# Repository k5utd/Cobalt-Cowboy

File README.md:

# Cobalt-Cowboy

A RISC-V-based digital mode radio running OpenRTX Radio Firmware

The goal of this project is to make available a hackable radio development platform for evaluating radio transceivers and experimenting with amateur multi-mode radio technology.

The intended users of this project include licenced Amateur Radio operators and students.

> [!NOTE]
> This repository includes the PCB, Schematic, and associated [KiCAD](https://www.kicad.org/) project files, as well as a parts list and any information necessary to build your own Cobalt Cowboy.

## Background

### OpenRTX Real-Time Operating Systems

This project intends to leverage the growing RF vendor support of Zephyr Project [ZephyrRTOS](https://zephyrproject.org/learn-about/).

The [OpenRTX firmware](https://openrtx.org) is an RTOS-agnostic application built from the ground-up with digital mode radios (DMR) in mind, some of which support the M17 protocol with hardware modification after firmware flashing.

The OpenRTX firmware typically uses the [Miosix](https://miosix.org/) kernel, primarily supporting STM32 targets on the ARM Cortex-M4F architecture, and is being ported to ZephyrRTOS to take advantage of support for more architectures.

### M17 Digital Mode and Codec2

For the purposes of this project, having multiple vocoder options to choose from for digital mode operation is desirable for reducing vendor lockin and avoiding product obsolescence.

The [M17 Project](https://m17project.org/) M17 RF protocol is an open protocol specification that leverages [Codec2](https://en.wikipedia.org/wiki/Codec_2) instead of DVSI [AMBE](https://en.wikipedia.org/wiki/Multi-Band_Excitation). 

Codec2 allows for open implementations as a software-defined vocoding alternative to DVSI vocoding hardware, complimenting the open communication stack of M17.

### Limitations and Alternatives 

The LILYGO [T-TWR Plus](https://www.lilygo.cc/products/t-twr-rev2-1) is a development board for evaluating the `NiceRF SA868` Walkie Talkie and `Quectel L76K` GNSS modules. The T-TWR Plus is as of September 2023 what motivated the OpenRTX team to begin porting OpenRTX to ZephyrRTOS. As of July 2024, rev2.1 now shows promise for experimenting with software-defined digital mode radio on VHF or UHF with improved RF module interfacing.

LILYGO has maintains a [repository](https://github.com/Xinyuan-LilyGO/T-TWR) of example testing firmware and schematics, However, the T-TWR Plus is not necessarily open source hardware, being schematic-available with no manufacturing files. NiceRF does not maintain public factory firmware of the SA868 either, so OpenRTX [sa8x8-fw](https://github.com/OpenRTX/sa8x8-fw) is necessary for use with OpenRTX.

## Getting Started

> [!IMPORTANT]
> This repository is primarily the hardware, the firmware and instructions are to be made available upstream OpenRTX.

### Board Fabrication

The board stackup is intended for OSHPark fabrication services.

The main board features an Espressif `ESP32-C3` and integrates the Texas Instruments `CC1200` Sub-Ghz transceiver. Most components are surface mount, and can get as small as `0602`.

### Firmware 
1. Set up the [Zephyr](https://docs.zephyrproject.org/latest/develop/getting_started/index.html) development environment
2. Set up the [Zephyr-based target toolchain](https://openrtx.org/#/compiling?id=compiling-a-zephyr-based-target) for OpenRTX
3. TODO: Build and compile an OpenRTX image for the `cobalt-cowboy` target

## Contact

To reach out, please join the Discord server.

CO: [Eric Mutton](https://github.com/ericmutton), username `cyndre`.

## License

This project is released under the GNU GPL v3.

See [LICENSE](LICENSE)

## Credits

Our thanks go to the following organizations for their efforts and advice:
* [M17 Project](https://m17project.org/) for their digital radio protocol for data and voice
* [OpenRTX](https://openrtx.org) for their radio firmware for digital mode radios and ham devices

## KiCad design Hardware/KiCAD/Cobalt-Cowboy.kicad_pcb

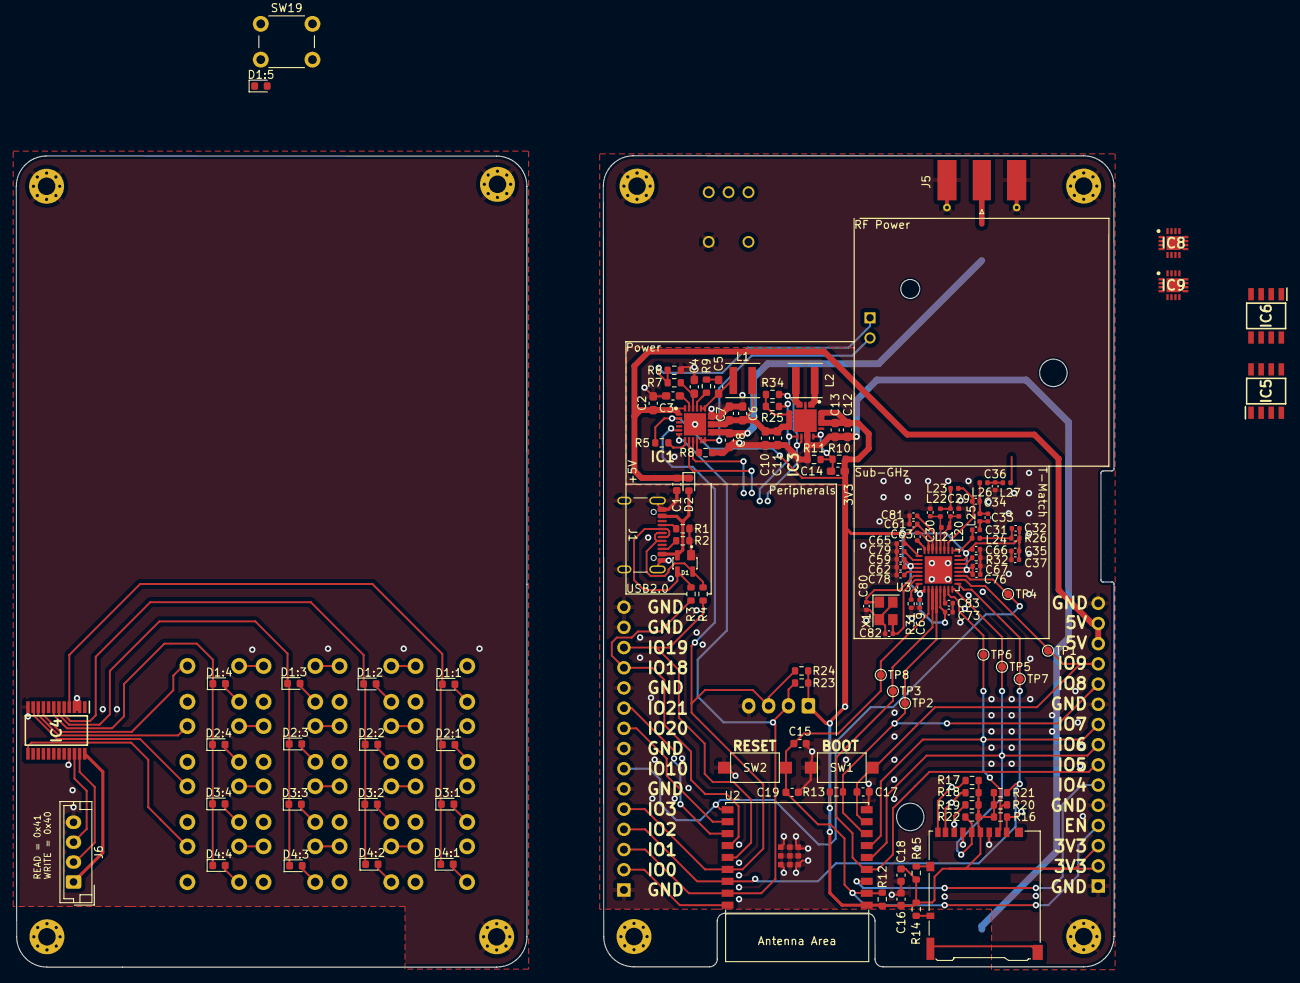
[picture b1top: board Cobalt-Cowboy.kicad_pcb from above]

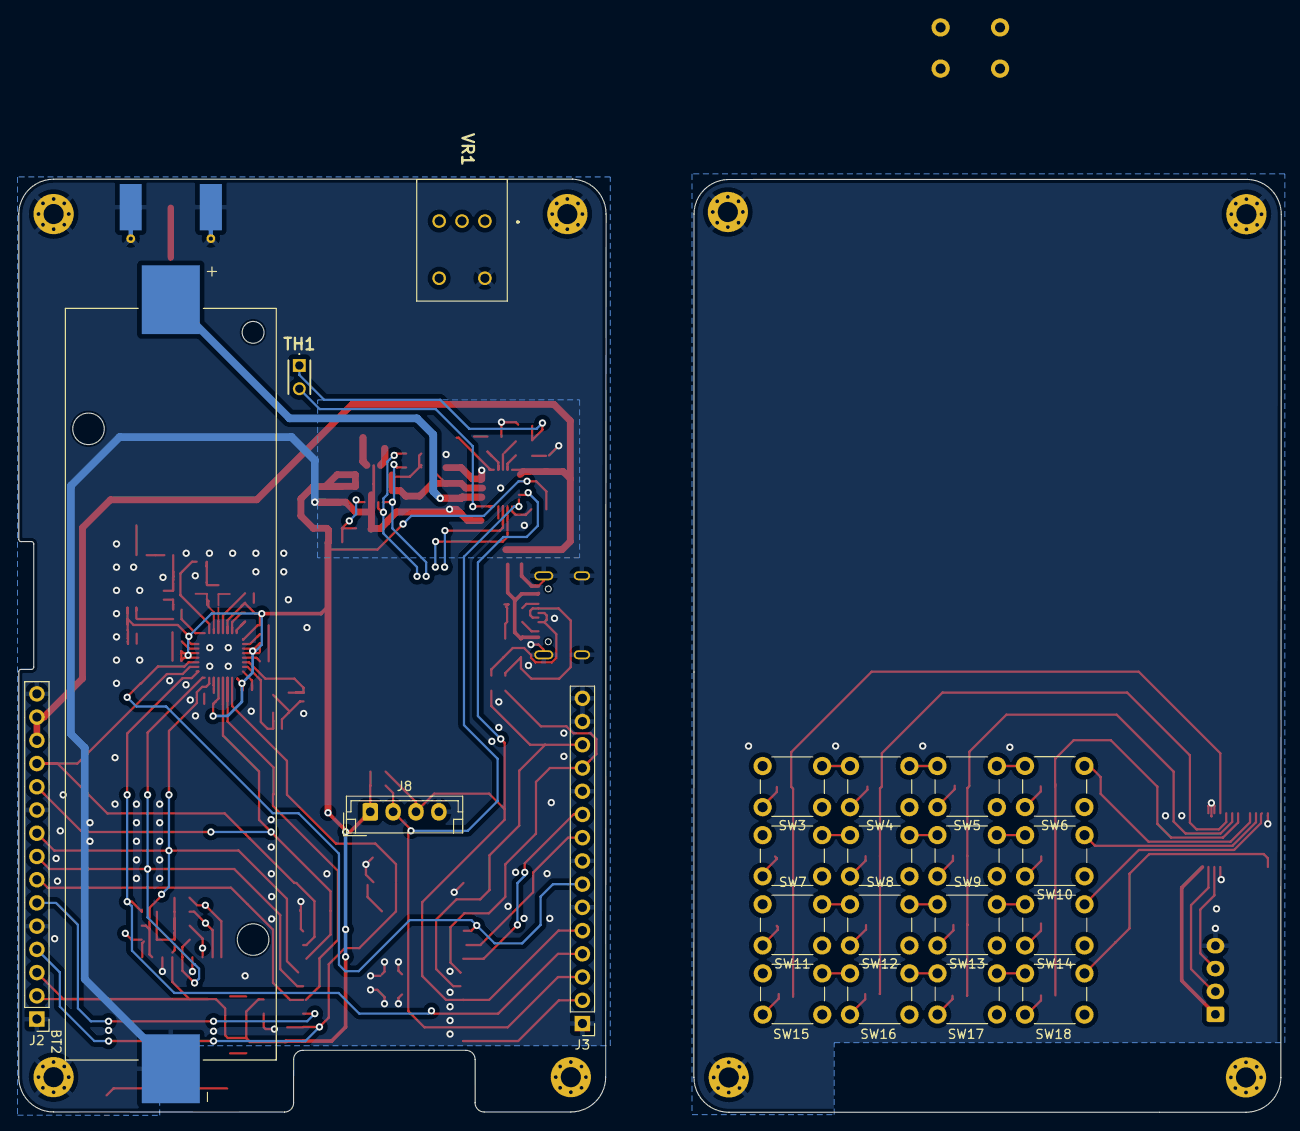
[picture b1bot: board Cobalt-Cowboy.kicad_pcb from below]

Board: 2 copper layers, 138.1 x 102.0 mm, 156 parts (22 on the bottom side), 98 nets.

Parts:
BT2: 1122; BAT_1122
C1, C16: 10u; C_0603_1608Metric
C2, C3: 1u; C_0603_1608Metric_Pad1.08x0.95mm_HandSolder
C4: 1uF; C_0603_1608Metric_Pad1.08x0.95mm_HandSolder
C5: 47n; C_0603_1608Metric_Pad1.08x0.95mm_HandSolder
C6, C7, C8, C10, C11: 10u; C_0603_1608Metric_Pad1.08x0.95mm_HandSolder
C12, C13: 22u; C_0603_1608Metric_Pad1.08x0.95mm_HandSolder
C14: 56p; C_0603_1608Metric_Pad1.08x0.95mm_HandSolder
C15: 1u; C_0603_1608Metric
C17, C18, C19: 0.1u; C_0603_1608Metric
C29, C30, C34: 5.1p; C_0402_1005Metric
C31: 39p; C_0402_1005Metric
C32: 56p; C_0402_1005Metric
C33: 2.2p; C_0402_1005Metric
C35, C81: 10n; C_0402_1005Metric
C36: 6.2p; C_0402_1005Metric
C37: 100p; C_0402_1005Metric
C59, C61, C62, C65, C66, C67, C69, C73, C76, C78, C79: 47n; C_0402_1005Metric
C63: 1.5n; C_0402_1005Metric
C80, C82: 15p; C_0402_1005Metric
C83: 220n; C_0402_1005Metric
D1: SP0503BAHTG; SOT143
D1:1, D1:2, D1:3, D1:4, D1:5, D2:1, D2:2, D2:3, D2:4, D3:1, D3:2, D3:3, D3:4, D4:1, D4:2, D4:3, D4:4: D; D_0603_1608Metric
D2: 1N5819; D_0603_1608Metric
IC1: BQ24193RGER; QFN50P400X400X100-25N-D_BQ24193RGER
IC3: ISL91127IRNZ-T7A; QFN50P400X400X100-21N_ISL91127IRNZ-T7A
IC4: PCF8575PWR; SOP65P640X120-24N_PCF8575PWR
IC5, IC6: SA630D_01,118; SOIC127P600X175-8N_SA630D_01,118
IC8, IC9: GRF5504; QFN50P300X300X90-17N_GRF5504
J1: USB_C_Receptacle; USB_C_Receptacle_GCT_USB4105-xx-A_16P_TopMnt_Horizontal
J2, J3: 1x15; PinHeader_1x15_P2.54mm_Vertical
J4: SD_Card; microSD_HC_Hirose_DM3AT-SF-PEJM5
J5: Conn_Coaxial_UHF; SMA_Molex_73251-1153_EdgeMount_Horizontal
J6, J8: Peripherals; JST_EH_B4B-EH-A_1x04_P2.50mm_Vertical
L1: 2.2u; L_Coilcraft_XxL4020
L2: 1u; L_Coilcraft_XxL4020
L20, L22: 27n; L_0402_1005Metric
L21, L24: 56n; L_0402_1005Metric
L23, L25: 15n; L_0402_1005Metric
L26: 43n; L_0402_1005Metric
L27: 22n; L_0402_1005Metric
R1: 5.1K; R_0603_1608Metric
R2: 5.1k; R_0603_1608Metric
R3, R4: 0k; R_0603_1608Metric
R5, R12, R13, R14, R15, R16, R17, R18, R19, R20, R21, R22, R23, R24, R25, R34: 10k; R_0603_1608Metric
R6: 6.86k; R_0603_1608Metric
R7: 2.27k; R_0603_1608Metric
R8: 265R; R_0603_1608Metric
R9: 0R; R_0603_1608Metric
R10: 1M; R_0603_1608Metric
R11: 2.2M; R_0603_1608Metric
R26: 18; R_0402_1005Metric
R31: 0R; R_0402_1005Metric
R32: 56k; R_0402_1005Metric
REF1, REF2, REF3, REF4, REF5, REF6, REF7, REF8: Conn_01x01; MountingHole_2.2mm_M2_Pad_Via
SW1, SW2: SW_Push; SW_SPST_CK_RS282G05A3
SW3: MENU; SW_PUSH_6mm_H7.3mm
SW4: UP; SW_PUSH_6mm_H7.3mm
SW5: DOWN; SW_PUSH_6mm_H7.3mm
SW6: EXIT; SW_PUSH_6mm_H7.3mm
SW7: 1; SW_PUSH_6mm_H7.3mm
SW8: 2; SW_PUSH_6mm_H7.3mm
SW9: 3; SW_PUSH_6mm_H7.3mm
SW10: *; SW_PUSH_6mm_H7.3mm
SW11: 4; SW_PUSH_6mm_H7.3mm
SW12: 5; SW_PUSH_6mm_H7.3mm
SW13: 6; SW_PUSH_6mm_H7.3mm
SW14: 0; SW_PUSH_6mm_H7.3mm
SW15: 7; SW_PUSH_6mm_H7.3mm
SW16: 8; SW_PUSH_6mm_H7.3mm
SW17: 9; SW_PUSH_6mm_H7.3mm
SW18: #; SW_PUSH_6mm_H7.3mm
SW19: PTT; SW_PUSH_6mm_H7.3mm
TH1: 103AT-2; 103AT2
TP1, TP2, TP3, TP4, TP5, TP6, TP7, TP8: TestPoint; TestPoint_Pad_D1.0mm
U2: ESP32-C3-WROOM-02
U3: CC1200RHBR; QFN-32-1EP_5x5mm_P0.5mm_EP3.45x3.45mm
VR1: RK09711110EL
X1: 40 MHz; Crystal_SMD_3225-4Pin_3.2x2.5mm

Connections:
3.3V: C12.1, C13.1, C14.1, C16.1, C18.2, C32.1, C35.1, C37.1, C59.1, C61.1, C62.1, C65.1, C66.1, C67.1, C69.1, C73.1, C76.1, IC1.2 (PSEL), IC3.17 (VOUT_1), IC3.18 (VOUT_2), IC3.19 (VOUT_3), IC3.20 (VOUT_4), IC4.24 (VCC), J2.2, J2.3, J4.4 (VDD), J6.1, J8.1, R5.1, R10.1, R12.2, R13.2, R14.2, R15.2, R16.2, R17.2, R18.2, R19.2, R20.2, R21.2, R22.2, R23.1, R24.1, R26.1, U2.1 (3V3), U3.1 (VDD_GUARD), U3.5 (DVDD), U3.12 (DVDD), U3.13 (AVDD_IF), U3.15 (AVDD_RF), U3.22 (AVDD_SYNTH1), U3.25 (AVDD_PFD_CHP), U3.27 (AVDD_SYNTH2), U3.28 (AVDD_XOSC)
+BATT: BT2.P, C8.1, IC1.13 (BAT_1), IC1.14 (BAT_2)
/Antenna_System/Amplifier_Assembly/5v_Amplifier_VCC: IC8.12 (BIAS), IC9.12 (BIAS)
/Antenna_System/LNA_N: C30.1, L21.2, L22.1, U3.20 (LNA_N)
/Antenna_System/LNA_P: C29.1, L20.1, L21.1, U3.19 (LNA_P)
/Antenna_System/PA: C31.2, L24.1, U3.17 (PA)
/Antenna_System/RF_Signal: IC5.3 (INPUT), L27.2
/Antenna_System/TRX_SW: C34.2, L23.1, U3.18 (TRX_SW)
/Communications_System/CC_X1: C80.2, U3.30 (XOSC_Q1), X1.1
/Communications_System/CC_X2: C82.1, U3.31 (XOSC_Q2), X1.3
/Computing_System/GPIO0: J3.2, U2.18 (GPIO0/ADC1_CH0/XTAL_32K_P)
/Computing_System/GPIO4: J2.6, U2.3 (GPIO4/ADC1_CH4)
/Computing_System/GPIO5: J2.7, TP3.1, U2.4 (GPIO5/ADC2_CH0), U3.3 (GPIO3)
/Computing_System/GPIO8: J2.11, R13.1, TP2.1, U2.7 (GPIO8), U3.4 (GPIO2)
/Computing_System/GPIO9: C17.2, J2.12, SW1.2, TP1.1, U2.8 (GPIO9), U3.10 (GPIO0)
/Computing_System/GPIO10: J3.7, TP4.1, U2.10 (GPIO10), U3.11 (~CS)
/Computing_System/I2C0_SCL: IC1.5 (SCL), IC4.22 (SCL), J3.5, J6.3, J8.3, R24.2, U2.15 (GPIO3/ADC1_CH3)
/Computing_System/I2C0_SDA: IC1.6 (SDA), IC4.23 (SDA), J3.3, J6.2, J8.2, R23.2, U2.17 (GPIO1/ADC1_CH1/XTAL_32K_N)
/Computing_System/Keypad/COL1: D1:1.1 (K), D2:1.1 (K), D3:1.1 (K), D4:1.1 (K), IC4.4 (P00)
/Computing_System/Keypad/COL2: D1:2.1 (K), D2:2.1 (K), D3:2.1 (K), D4:2.1 (K), IC4.5 (P01)
/Computing_System/Keypad/COL3: D1:3.1 (K), D2:3.1 (K), D3:3.1 (K), D4:3.1 (K), IC4.6 (P02)
/Computing_System/Keypad/COL4: D1:4.1 (K), D2:4.1 (K), D3:4.1 (K), D4:4.1 (K), IC4.7 (P03)
/Computing_System/Keypad/COL5: D1:5.1 (K), IC4.8 (P04)
/Computing_System/Keypad/ROW1: IC4.9 (P05), SW3.2, SW4.2, SW5.2, SW6.2, SW19.2
/Computing_System/Keypad/ROW2: IC4.10 (P06), SW7.2, SW8.2, SW9.2, SW10.2
/Computing_System/Keypad/ROW3: IC4.11 (P07), SW11.2, SW12.2, SW13.2, SW14.2
/Computing_System/Keypad/ROW4: IC4.13 (P10), SW15.2, SW16.2, SW17.2, SW18.2
/Computing_System/RST: C15.2, C19.2, J2.4, R12.1, SW2.2, TP8.1, U2.2 (EN/CHIP_PU), U3.2 (~RESET)
/Computing_System/SD_DAT0: J4.7 (DAT0), R19.1
/Computing_System/SD_DAT1: J4.8 (DAT1), R18.1
/Computing_System/SD_DAT2: J4.9 (DAT2), R17.1
/Computing_System/SD_DAT3: J4.1 (CD/DAT3), R16.1
/Computing_System/SPIM2_MISO: J3.4, R21.1, TP7.1, U2.16 (GPIO2/ADC1_CH2), U3.9 (SO(GPIO1))
/Computing_System/SPIM2_MOSI: J2.9, J4.2 (CMD), R20.1, TP6.1, U2.6 (GPIO7), U3.7 (SI)
/Computing_System/SPIM2_SCLK: J2.8, J4.5 (CLK), R22.1, TP5.1, U2.5 (GPIO6), U3.8 (SCLK)
/Computing_System/UART0_RX: J3.9, U2.11 (GPIO20/U0RXD)
/Computing_System/UART0_TX: J3.10, U2.12 (GPIO21/U0TXD)
/Computing_System/~SD_CD: J4.10 (CARD_DETECT), R14.1
/Computing_System/~SD_WP: J4.11 (WRITE_PROTECT), R15.1
/Power_System/BMS_INT: IC1.7 (INT), R5.2
/Power_System/V_{SYS}: C6.2, C7.2, C10.2, C11.2, IC1.15 (SYS_1), IC1.16 (SYS_2), IC3.6 (PVIN_1), IC3.7 (PVIN_2), IC3.8 (PVIN_3), IC3.9 (PVIN_4), IC3.10 (VIN), L1.2, R25.1, R34.2
/USB_DN: J3.12, R3.2, U2.13 (GPIO18/USB_D-)
/USB_DP: J3.13, R4.1, U2.14 (GPIO19/USB_D+)
GND: BT2.N, C1.2, C2.2, C3.2, C4.1, C6.1, C7.1, C8.2, C10.1, C11.1, C12.2, C13.2, C15.1, C16.2, C17.1, C18.1, C19.1, C30.2, C35.2, C36.2, C37.2, C59.2, C61.2, C62.2, C65.2, C66.2, C67.2, C69.2, C73.2, C76.2, C78.2, C79.2, C80.1, C81.2, C82.2, C83.2, D1.1, IC1.17 (PGND_1), IC1.18 (PGND_2), IC1.25 (EP), IC3.3 (PGND), IC3.13 (SGND_1), IC3.14 (SGND_2), IC3.21 (EPAD), IC4.2 (A1), IC4.3 (A2), IC4.12 (GND), IC4.21 (A0), IC8.2 (GND/NC_1), IC8.5 (GND/NC_2), IC8.6 (GND/NC_3), IC8.7 (GND/NC_4), IC8.8 (GND/NC_5), IC8.11 (GND/NC_6), IC8.14 (GND/NC_7), IC8.15 (GND/NC_8), IC8.17 (GND), IC9.2 (GND/NC_1), IC9.5 (GND/NC_2), IC9.6 (GND/NC_3), IC9.7 (GND/NC_4), IC9.8 (GND/NC_5), IC9.11 (GND/NC_6), IC9.14 (GND/NC_7), IC9.15 (GND/NC_8), IC9.17 (GND), J1.A1 (GND), J1.A12 (GND), J1.B1 (GND), J1.B12 (GND), J1.S1 (SHIELD), J2.1, J2.5, J2.10, J2.15, J3.1, J3.6, J3.8, J3.11, J3.14, J3.15, J4.3 (VSS), J4.6 (VSS), J5.2 (Ext), J6.4, J8.4, L20.2, R1.1, R2.1, R6.2, R8.2, R11.2, R31.1, R32.2, REF1.1, REF2.1, REF3.1, REF4.1, REF5.1, REF6.1, REF7.1, REF8.1, SW1.1, SW2.1, U2.9 (GND), U2.19 (GND), U3.33 (GND_EP), VR1.4 (COM), X1.2, X1.4
unnamed: C5.1, R9.1
unnamed: C29.2, L22.2, L23.2
unnamed: C31.1, C33.2, L25.1
unnamed: C32.2, L24.2, R26.2
unnamed: C33.1, C34.1, L25.2, L26.1
unnamed: C36.1, L26.2, L27.1
unnamed: D1.3, J1.A7 (D-), J1.B7 (D-), R3.1
unnamed: D1.4, J1.A6 (D+), J1.B6 (D+), R4.2
unnamed: D1:1.2 (A), SW3.1
unnamed: D1:2.2 (A), SW4.1
unnamed: D1:3.2 (A), SW5.1
unnamed: D1:4.2 (A), SW6.1
unnamed: D1:5.2 (A), SW19.1
unnamed: D2:1.2 (A), SW7.1
unnamed: D2:2.2 (A), SW8.1
unnamed: D2:3.2 (A), SW9.1
unnamed: D2:4.2 (A), SW10.1
unnamed: D3:1.2 (A), SW11.1
unnamed: D3:2.2 (A), SW12.1
unnamed: D3:3.2 (A), SW13.1
unnamed: D3:4.2 (A), SW14.1
unnamed: D4:1.2 (A), SW15.1
unnamed: D4:2.2 (A), SW16.1
unnamed: D4:3.2 (A), SW17.1
unnamed: D4:4.2 (A), SW18.1
unnamed: IC1.21 (BTST), R9.2
unnamed: IC1.10 (ILIM), R8.1
unnamed: C3.1, IC1.23 (PMID)
unnamed: C4.2, IC1.22 (REGN), R7.1
unnamed: C5.2, IC1.19 (SW_1), IC1.20 (SW_2), L1.1
unnamed: IC1.11 (TS1), IC1.12 (TS2), TH1.2
unnamed: IC3.11 (EN), R25.2
unnamed: C14.2, IC3.15 (FB), R10.2, R11.1
unnamed: IC3.4 (LX1_1), IC3.5 (LX1_2), L2.1
unnamed: IC3.1 (LX2_1), IC3.2 (LX2_2), L2.2
unnamed: IC3.12 (MODE), R34.1
unnamed: IC6.3 (INPUT), J5.1 (In)
unnamed: IC8.3 (RF_IN_1), IC8.4 (RF_IN_2)
unnamed: IC8.9 (RF_OUT/VCC2_1), IC8.10 (RF_OUT/VCC2_2)
unnamed: IC9.3 (RF_IN_1), IC9.4 (RF_IN_2)
unnamed: IC9.9 (RF_OUT/VCC2_1), IC9.10 (RF_OUT/VCC2_2)
unnamed: J1.A5 (CC1), R1.2
unnamed: J1.B5 (CC2), R2.2
unnamed: R6.1, R7.2, TH1.1
unnamed: C83.1, U3.6 (DCPL)
unnamed: C79.1, U3.26 (DCPL_PFD_CHP)
unnamed: C81.1, U3.21 (DCPL_VCO)
unnamed: C78.1, U3.29 (DCPL_XOSC)
unnamed: R31.2, U3.32 (EXT_XOSC)
unnamed: C63.2, U3.23 (LPF0)
unnamed: C63.1, U3.24 (LPF1)
unnamed: R32.1, U3.14 (RBIAS)
VBUS: D1.2, D2.2 (A), J1.A4 (VBUS), J1.A9 (VBUS), J1.B4 (VBUS), J1.B9 (VBUS)
VCC_5V: C1.1, C2.1, D2.1 (K), IC1.1 (VBUS_1), IC1.24 (VBUS_2), J2.13, J2.14

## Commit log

2023-10-08 Initialize KiCAD project
2023-10-08 Give a slightly better description
2023-10-08 Clarify repo contents and M17 support
2023-10-09 Added Basic Layout, as well as created library file and added symbols
2023-10-15 chore: Include CC1200RHBR model
2023-10-15 chore: Remove and ignore local KiCAD backups
2023-10-16 fix: Update C3 to reference footprint, symbol
2023-10-16 chore: switch to lowercase file extension
2023-10-16 feat: Connect ESP32 to CC1200
2023-10-16 chore: ignore KiCAD cache and table files
2023-10-16 fix: Change some global labels to heirarchical
2023-10-21 feat: add models, correct hierarchical patterns
2023-10-23 added battery to start power systen
2023-10-31 added schematics
2023-10-31 removed useless files
2023-10-31 Renamed and added the kicad library
2023-11-18 Added a test for commit
2023-11-18 Added components for amplifier, RF switch, 5v Boost, renamed footprints
2023-11-18 feat: corrected Power routing, added TODOs for board, prepared for amps
2023-11-18 chore: Added plots for ease of viewing
2023-11-18 added keypad
2023-11-18 Chore: updated plots for ease of viewing
2023-11-18 Changed Keypad to better accomidate use of GPIO and removed inc symbols
2023-11-19 Added 3.3v converter
2023-11-19 Added a GND to USBC connector
2023-11-19 Chore: plotted changes for ease of viewing
2024-01-26 fix: revised GPIO pins for CC1200 SPI pins
2024-02-09 docs: Add draft Contributor's Guide #10
2024-03-10 Added seperate schematic for amplifier assembly
2024-03-10 Added biasing, Still need to add actual values
2024-05-29 feat: subsystem exploration, begin placement, routing #11 #12 #4 many new project symbols
2024-05-29 fix: correct malformed Edge.Cuts
2024-06-06 feat: Plot updated schematics #11
2024-08-07 Update README.md
    Long needed refresh and inclusion of project background. Also applied OpenRTX feedback.
2025-04-28 Create CODEOWNERS
    #2
